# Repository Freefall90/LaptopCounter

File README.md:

# LaptopCounter
An "accident counter" LED clock for a coworker who regularly leaves his laptop at home

We have this guy at work who will leave his computer at home pretty regularly. We got to joking about needing one of those LED "days since last accident" displays in the office. So I set about to create one.

It will count up to 999 days, can be manually set by rotating the dial, and reset by pushing the dial.

Oh yeah, the code and circuitry depends on having this LED clock screen I salvaged with some really weird common anode setup. So, it's probably not all that reusable. Sorry.

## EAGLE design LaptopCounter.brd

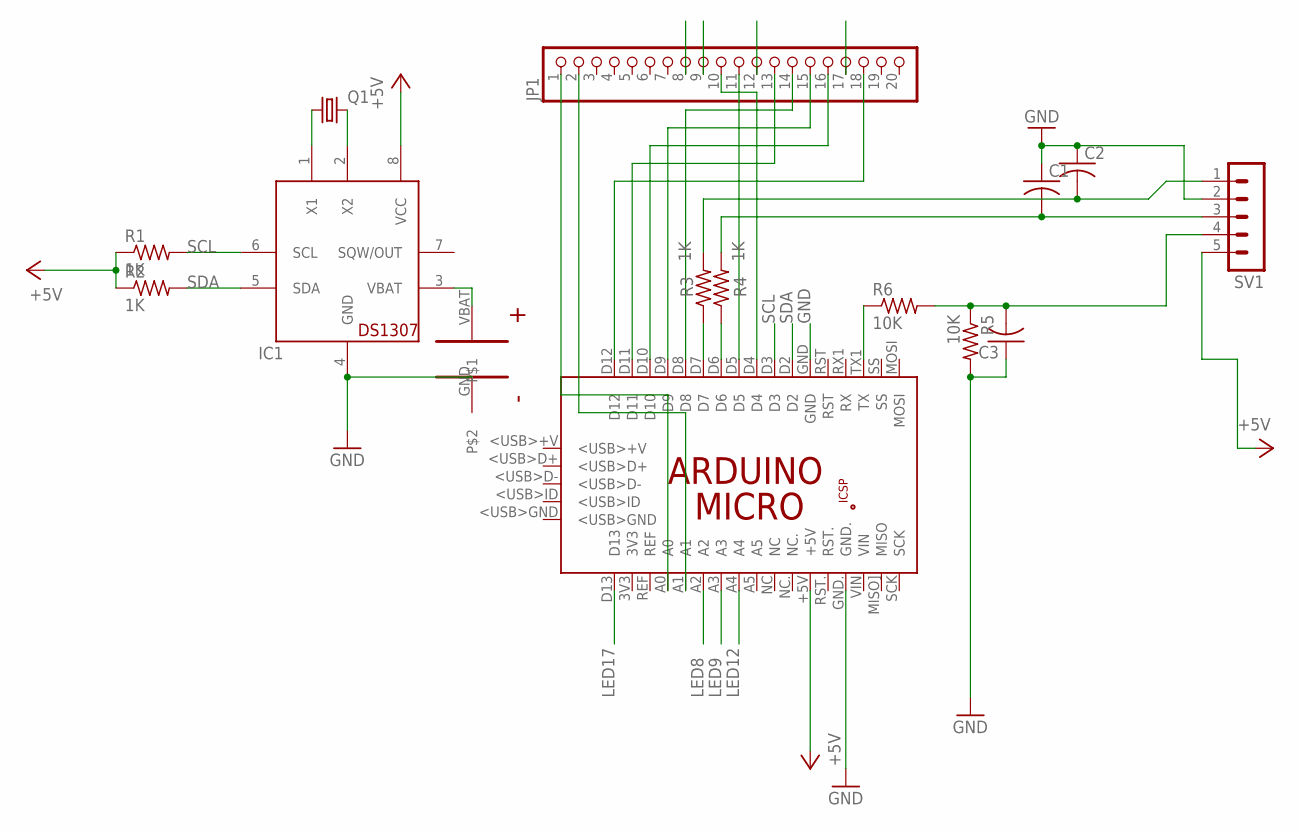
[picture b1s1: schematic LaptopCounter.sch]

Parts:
C1, C2, C3: C-US025-024X044; C025-024X044
IC1: DS1307; DIL08
JP1: PINHD-1X20; 1X20
PCB1: ARDUINO_MICRO
Q1: CRYSTALTC26H; TC26H
R1, R2, R3, R4: 1K; 0207/10
R5, R6: 10K; 0207/10
SV1: MA05-1
U$1: CR2032; 2PIN_TH

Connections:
+5V: IC1.8 (VCC), PCB1.+5V, R1.1, R2.1, SV1.5
GND: C1.1, C2.1, C3.1, IC1.4 (GND), PCB1.GND, PCB1.GND., R5.2, SV1.2, U$1.GND
LED8: JP1.8, PCB1.A2
LED9: JP1.9, PCB1.A3
LED12: JP1.12, PCB1.A4
LED17: JP1.17, PCB1.D13
unnamed: IC1.1 (X1), Q1.1
unnamed: IC1.2 (X2), Q1.2
unnamed: PCB1.D6, R4.1
unnamed: PCB1.D7, R3.1
unnamed: C1.2, R4.2, SV1.3
unnamed: C2.2, R3.2, SV1.1
unnamed: JP1.18, PCB1.D12
unnamed: JP1.13, PCB1.D11
unnamed: JP1.16, PCB1.D10
unnamed: JP1.15, PCB1.D9
unnamed: JP1.14, PCB1.D8
unnamed: JP1.11, PCB1.D5
unnamed: JP1.10, PCB1.D4
unnamed: PCB1.TX1 (TX), R6.1
unnamed: C3.2, R5.1, R6.2, SV1.4
unnamed: JP1.1, PCB1.A0
unnamed: JP1.2, PCB1.A1
unnamed: IC1.3 (VBAT), U$1.VBAT
SCL: IC1.6 (SCL), PCB1.D3, R1.2
SDA: IC1.5 (SDA), PCB1.D2, R2.2

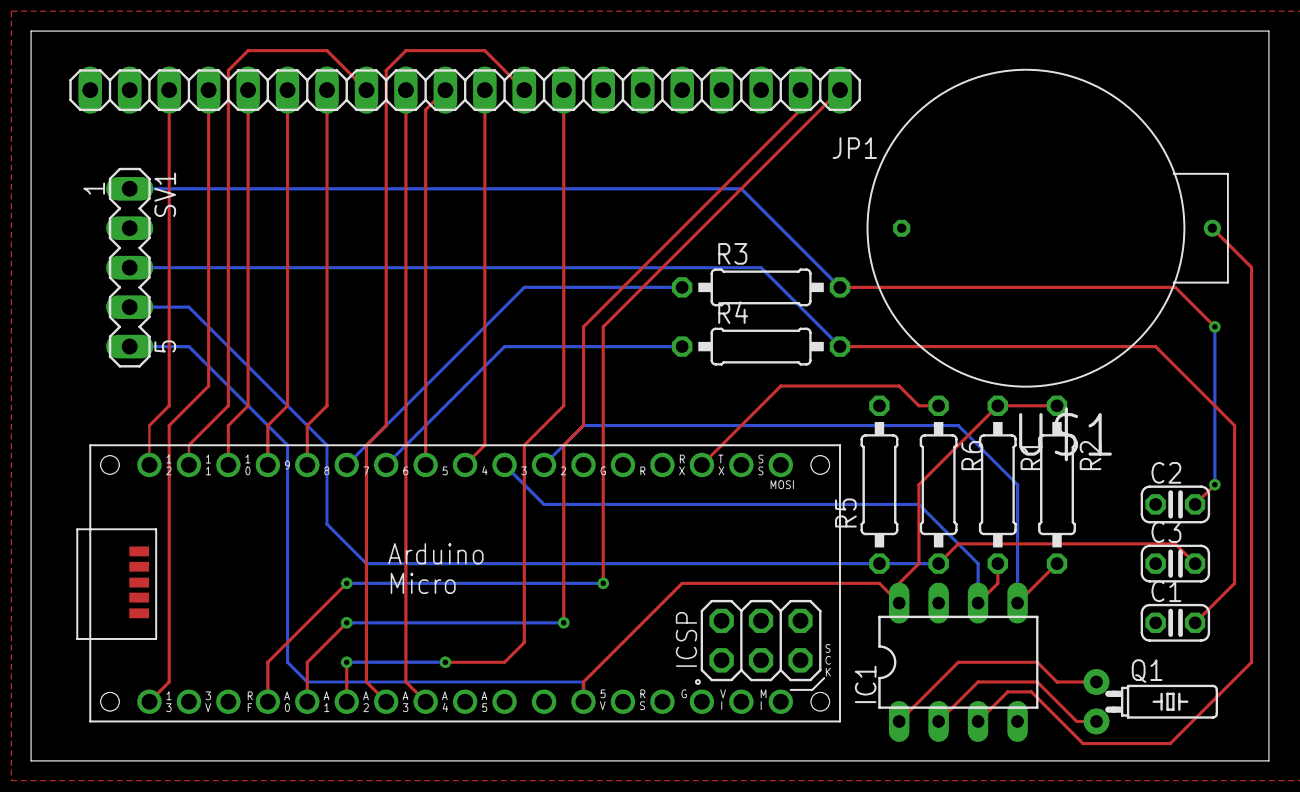
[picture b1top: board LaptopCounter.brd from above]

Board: 2 copper layers, 79.7 x 47.0 mm, 15 parts (0 on the bottom side), 26 nets.

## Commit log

2019-04-26 Initial commit.
2019-04-26 Adding gitignore
2019-04-26 Removing board history
2019-05-06 Initial stab at per-row LED light up
2019-05-08 Fixed valueArray order
2019-05-10 Updated loop logic
2019-05-10 Fixed brightness issue.
2019-05-11 Brightness fixed. Time setting fixed. Battery not required!
